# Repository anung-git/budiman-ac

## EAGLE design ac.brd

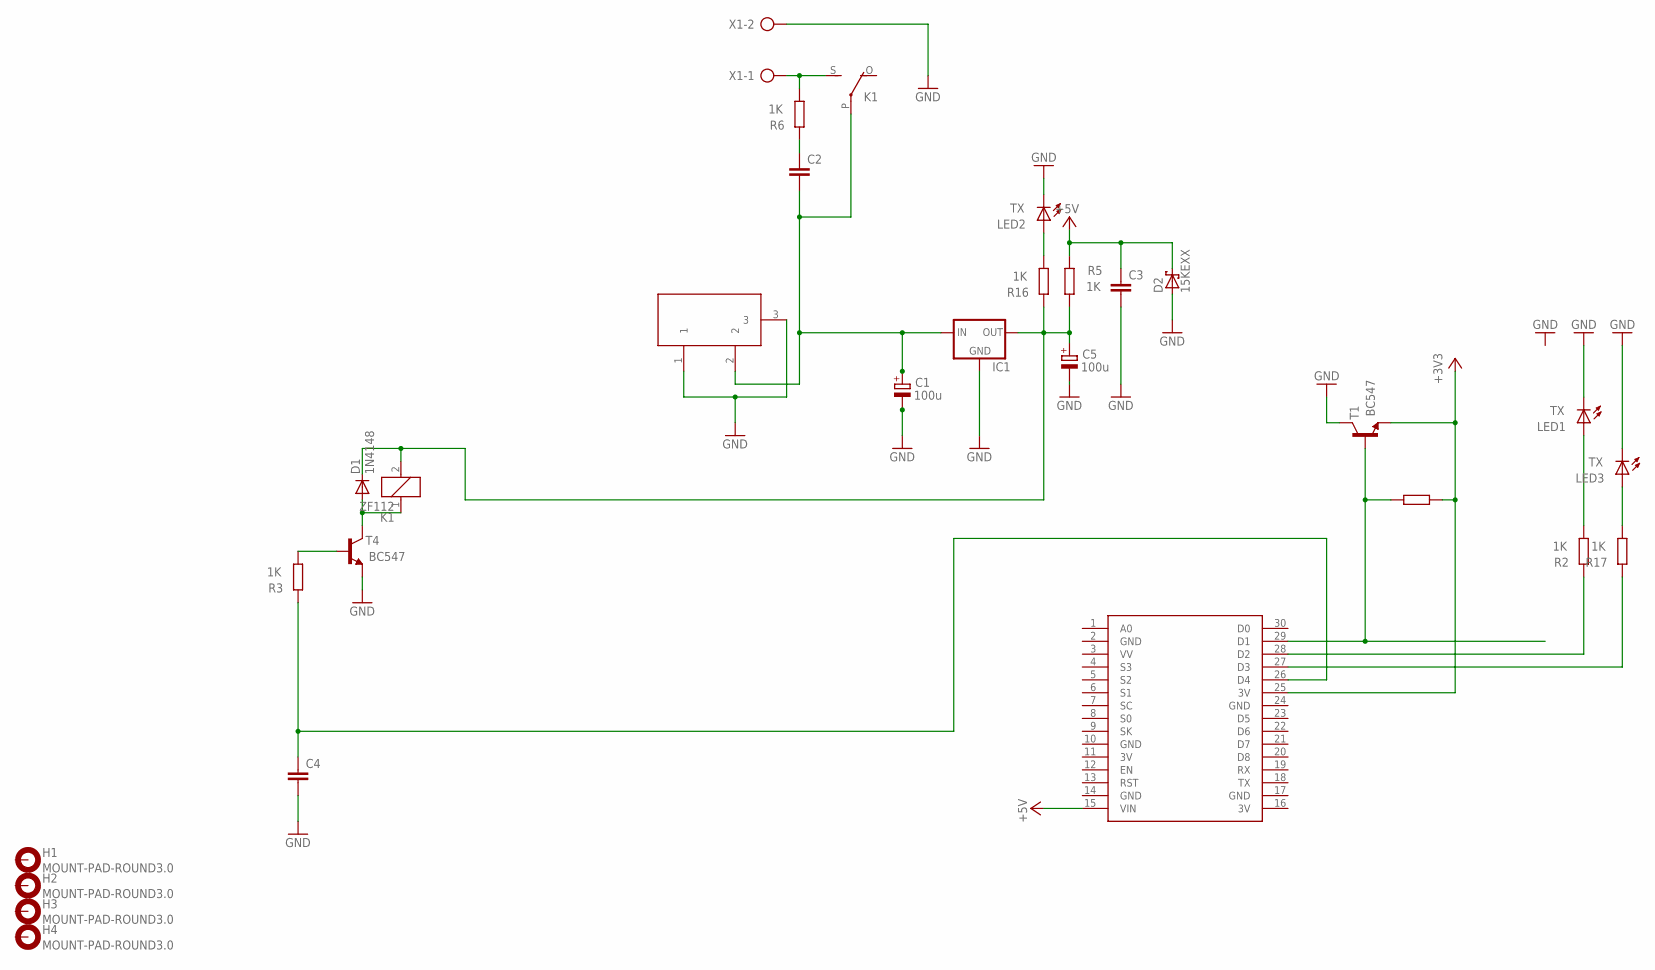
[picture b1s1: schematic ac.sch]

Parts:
C1, C5: 100u; E3,5-8
C2, C3, C4: C-EU102-043X133; C102-043X133
D1: 1N4148; DO35-10
D2: 15KEXX; CB429-17
DC1: DC21MMX; DC-21MM
H1, H2, H3, H4: MOUNT-PAD-ROUND3.0; 3,0-PAD
IC1: 78XXS
K1: ZF112
LED1, LED2, LED3: TX; LED5MM
R2, R3, R5, R6, R16, R17: 1K; 0207/10
R4: 1k; 0207/10
T1, T4: BC547; TO92
U$1: NODEMCU
X1: AK300/2

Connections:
3V: U$1.11 (3V), U$1.16 (3V)
+3V3: R4.1, T1.1 (E), U$1.25 (3V)
+5V: C3.1, D2.C, R5.2, U$1.15 (VIN)
GND: C1.-, C3.2, C4.2, C5.-, D2.A, DC1.1, DC1.3, IC1.GND, LED1.K (C), LED2.K (C), LED3.K (C), T1.3 (C), T4.1 (E), U$1.2 (GND), U$1.10 (GND), U$1.14 (GND), U$1.17 (GND), U$1.24 (GND), X1.2
unnamed: R3.1, T4.2 (B)
unnamed: K1.S, R6.1, X1.1
unnamed: D1.A, K1.1, T4.3 (C)
unnamed: C2.1, R6.2
unnamed: C1.+, C2.2, DC1.2, IC1.IN, K1.P
unnamed: C5.+, D1.C, IC1.OUT, K1.2, R5.1, R16.2
unnamed: R4.2, T1.2 (B), U$1.29 (D1)
unnamed: R2.2, U$1.28 (D2)
unnamed: R17.2, U$1.27 (D3)
unnamed: C4.1, R3.2, U$1.26 (D4)
unnamed: LED2.A, R16.1
unnamed: LED3.A, R17.1
unnamed: LED1.A, R2.1

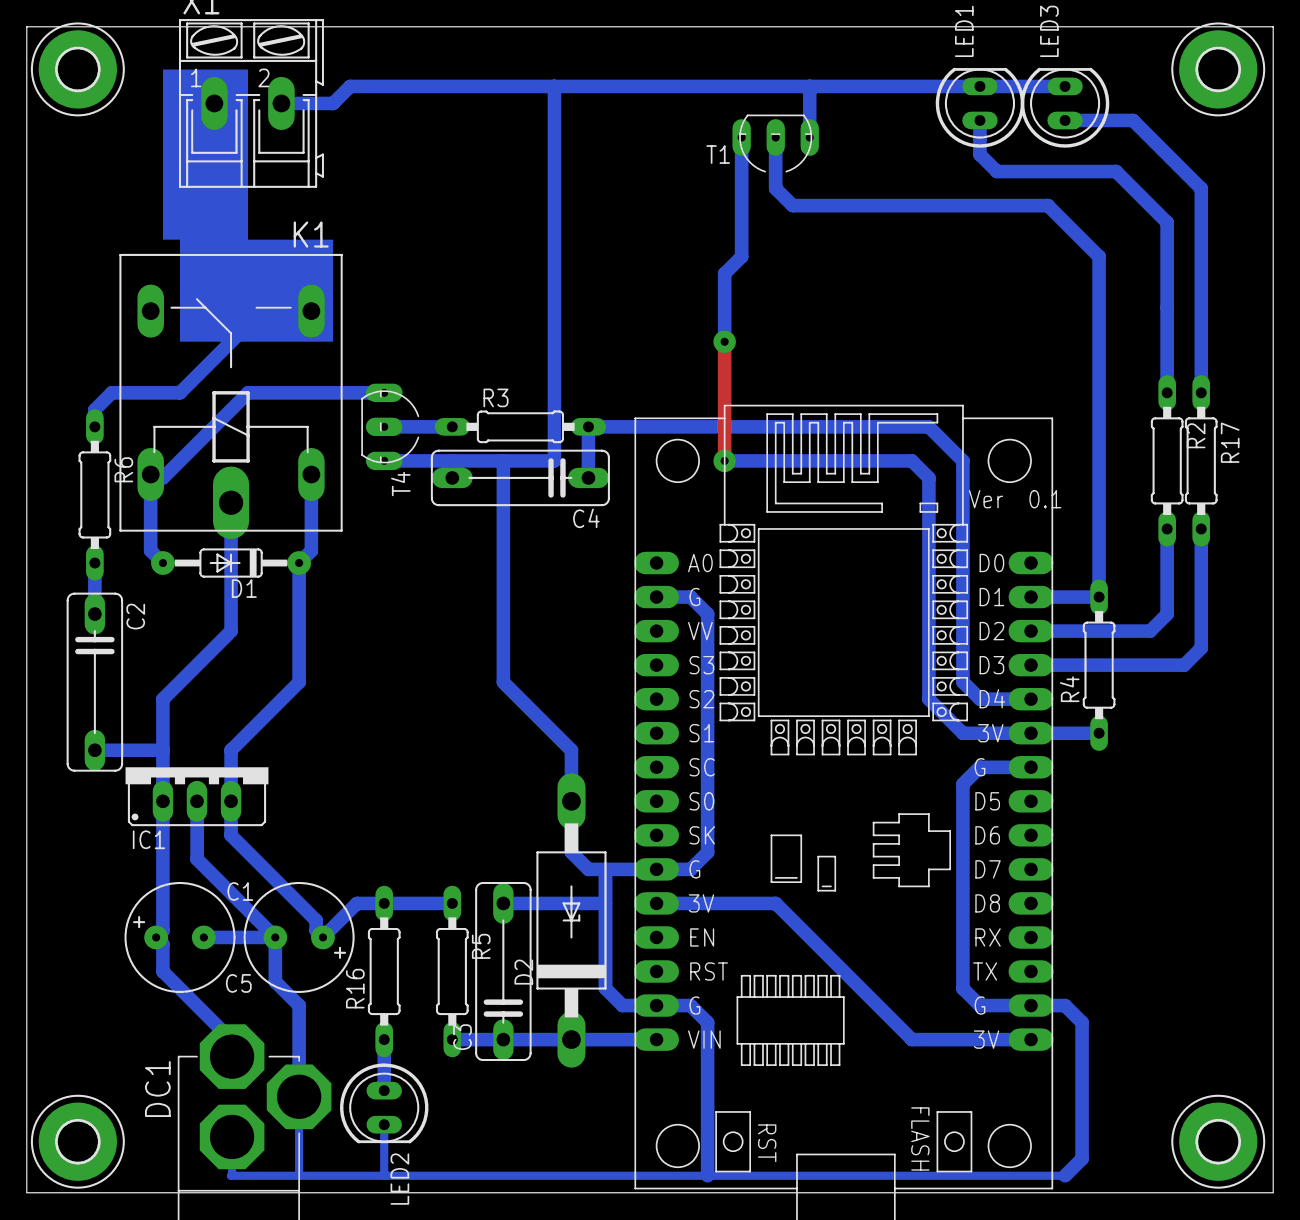
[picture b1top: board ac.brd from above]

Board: 2 copper layers, 93.0 x 87.0 mm, 28 parts (0 on the bottom side), 17 nets.

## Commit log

2020-04-25 upload
2020-04-26 mode
